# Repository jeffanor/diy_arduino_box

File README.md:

# diy_arduino_box
DIY Arduino E-Stim Unit

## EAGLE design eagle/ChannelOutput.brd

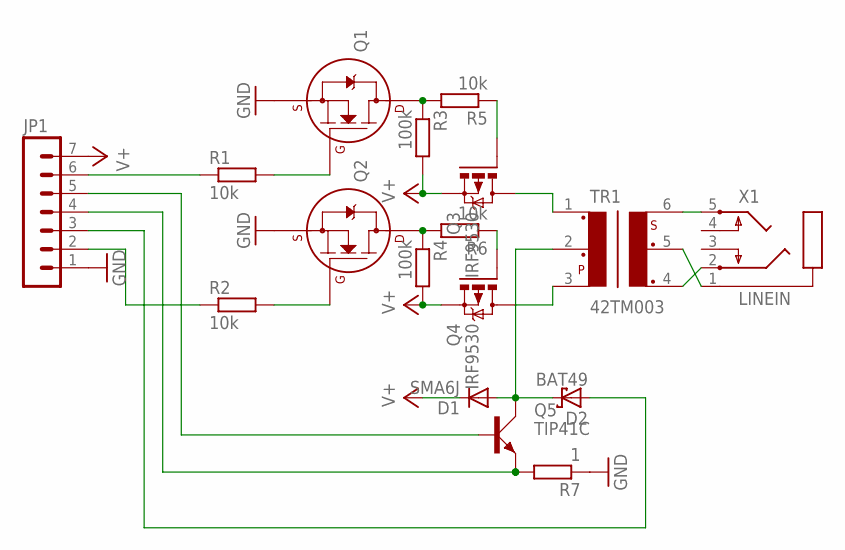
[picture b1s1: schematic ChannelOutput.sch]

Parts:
D1: SMA6J; DO41-10
D2: BAT49; DO41-10
JP1: MA07-1
Q1, Q2: 2N7000_TO92; TO-92
Q3, Q4: IRF9530; TO220BV
Q5: TIP41C; TO220AV
R1, R2, R5, R6: 10k; 0207/2V
R3, R4: 100k; 0204/5
R7: 1; 0207/2V
TR1: 42TM003; 42TM
X1: LINEIN; PG203J

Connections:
GND: JP1.1, Q1.1 (S), Q2.1 (S), R7.1
unnamed: Q1.2 (G), R1.2
unnamed: Q4.G, R6.1
unnamed: JP1.2, R2.1
unnamed: JP1.6, R1.1
unnamed: Q4.D, TR1.3
unnamed: Q3.D, TR1.1
unnamed: D2.A, JP1.3
unnamed: JP1.4, Q5.E, R7.2
unnamed: D1.A, D2.C, Q5.C, TR1.2
unnamed: TR1.6, X1.5
unnamed: TR1.5, X1.1
unnamed: TR1.4, X1.2
unnamed: Q2.3 (D), R4.1, R6.2
unnamed: Q3.G, R5.1
unnamed: Q1.3 (D), R3.1, R5.2
unnamed: Q2.2 (G), R2.2
unnamed: JP1.5, Q5.B
V+: D1.C, JP1.7, Q3.S, Q4.S, R3.2, R4.2

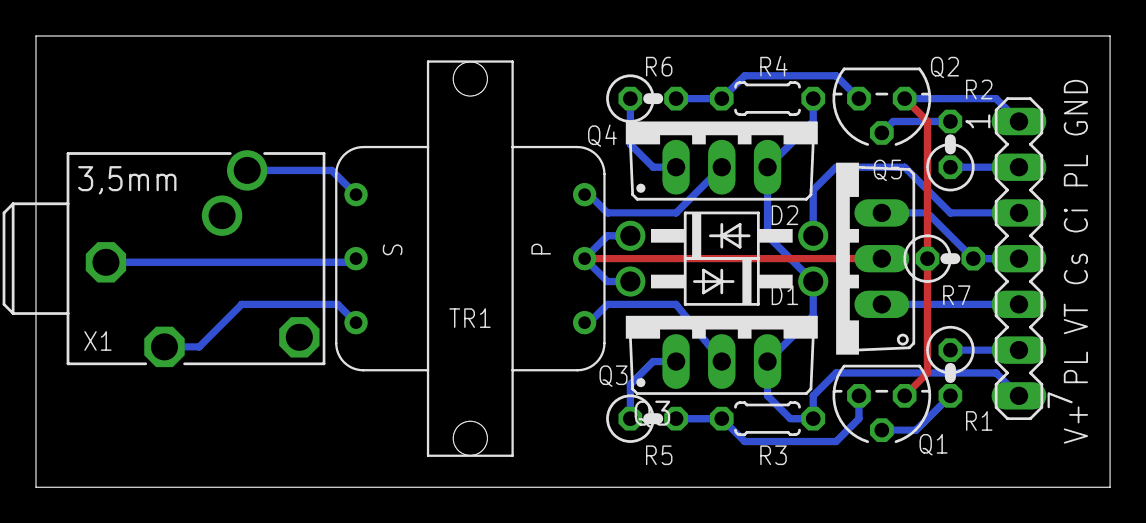
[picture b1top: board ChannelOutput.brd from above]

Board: 2 copper layers, 59.7 x 25.1 mm, 17 parts (0 on the bottom side), 19 nets.

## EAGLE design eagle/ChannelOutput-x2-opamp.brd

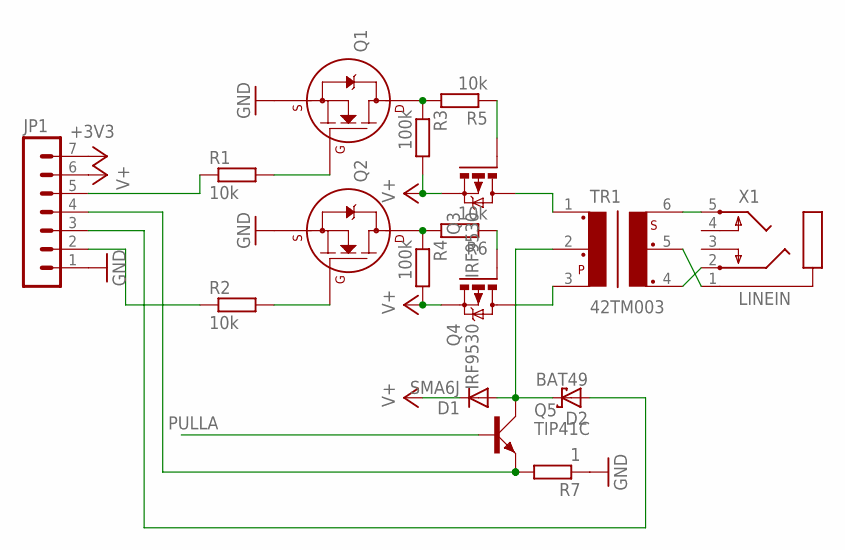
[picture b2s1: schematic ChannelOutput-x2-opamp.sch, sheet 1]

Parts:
D1: SMA6J; DO41-10
D2: BAT49; DO41-10
JP1: MA07-1
Q1, Q2: 2N7000_TO92; TO-92
Q3, Q4: IRF9530; TO220BV
Q5: TIP41C; TO220AV
R1, R2, R5, R6: 10k; 0207/2V
R3, R4: 100k; 0204/5
R7: 1; 0207/2V
TR1: 42TM003; 42TM
X1: LINEIN; PG203J

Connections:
+3V3: JP1.7; also elsewhere on the board
GND: JP1.1, Q1.1 (S), Q2.1 (S), R7.1; also elsewhere on the board
unnamed: Q1.2 (G), R1.2
unnamed: Q4.G, R6.1
unnamed: JP1.2, R2.1
unnamed: JP1.5, R1.1
unnamed: Q4.D, TR1.3
unnamed: Q3.D, TR1.1
unnamed: D2.A, JP1.3
unnamed: JP1.4, Q5.E, R7.2
unnamed: D1.A, D2.C, Q5.C, TR1.2
unnamed: TR1.6, X1.5
unnamed: TR1.5, X1.1
unnamed: TR1.4, X1.2
unnamed: Q2.3 (D), R4.1, R6.2
unnamed: Q3.G, R5.1
unnamed: Q1.3 (D), R3.1, R5.2
unnamed: Q2.2 (G), R2.2
PULLA: Q5.B; also elsewhere on the board
V+: D1.C, JP1.6, Q3.S, Q4.S, R3.2, R4.2; also elsewhere on the board

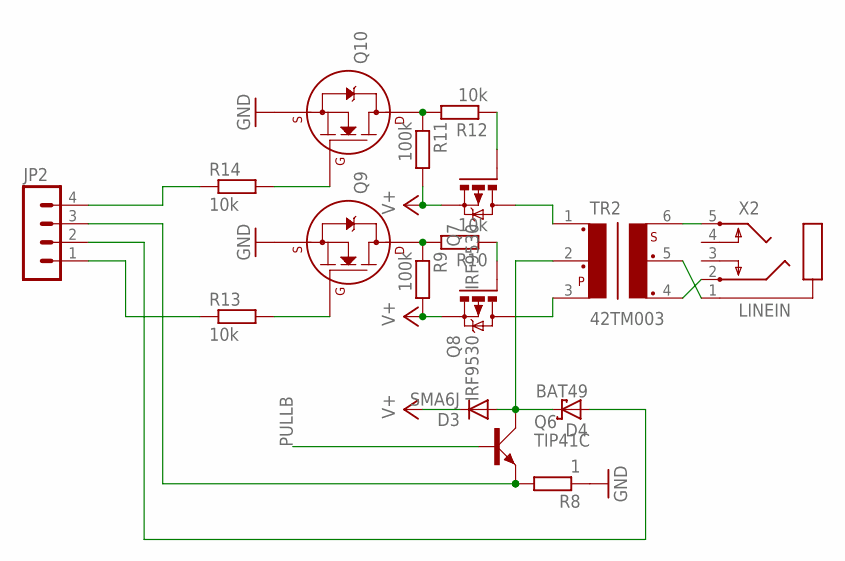
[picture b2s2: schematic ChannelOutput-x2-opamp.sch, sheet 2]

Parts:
D3: SMA6J; DO41-10
D4: BAT49; DO41-10
JP2: MA04-1
Q6: TIP41C; TO220AV
Q7, Q8: IRF9530; TO220BV
Q9, Q10: 2N7000_TO92; TO-92
R8: 1; 0207/2V
R9, R11: 100k; 0204/5
R10, R12, R13, R14: 10k; 0207/2V
TR2: 42TM003; 42TM
X2: LINEIN; PG203J

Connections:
GND: Q9.1 (S), Q10.1 (S), R8.1; also elsewhere on the board
unnamed: D3.A, D4.C, Q6.C, TR2.2
unnamed: TR2.6, X2.5
unnamed: TR2.5, X2.1
unnamed: TR2.4, X2.2
unnamed: JP2.3, Q6.E, R8.2
unnamed: Q9.3 (D), R9.1, R10.2
unnamed: Q7.G, R12.1
unnamed: Q10.3 (D), R11.1, R12.2
unnamed: Q9.2 (G), R13.2
unnamed: JP2.4, R14.1
unnamed: Q8.G, R10.1
unnamed: Q10.2 (G), R14.2
unnamed: JP2.1, R13.1
unnamed: Q8.D, TR2.3
unnamed: Q7.D, TR2.1
unnamed: D4.A, JP2.2
PULLB: Q6.B; also elsewhere on the board
V+: D3.C, Q7.S, Q8.S, R9.2, R11.2; also elsewhere on the board

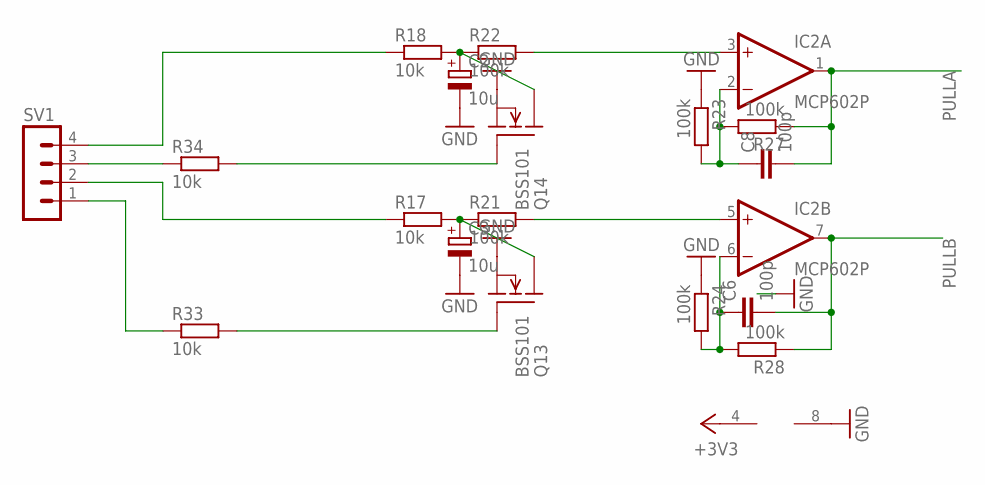
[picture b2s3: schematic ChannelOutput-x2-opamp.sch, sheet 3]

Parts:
C2, C3: 10u; TT2D5
C6, C8: 100p; C025-024X044
IC2: MCP602P; DIL08
Q13, Q14: BSS101; TO92
R17, R18, R33, R34: 10k; 0207/2V
R21, R22, R23, R24, R27, R28: 100k; 0207/2V
SV1: MA04-1

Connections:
+3V3: IC2.4 (V-); also elsewhere on the board
GND: C2.-, C3.-, IC2.8 (V+), Q13.1 (S), Q14.1 (S), R23.1, R24.1; also elsewhere on the board
unnamed: R34.1, SV1.3
unnamed: IC2.3 (+IN), R22.2
unnamed: R18.1, SV1.4
unnamed: C6.1, IC2.6 (-IN), R24.2, R28.2
unnamed: R17.1, SV1.2
unnamed: C8.1, IC2.2 (-IN), R23.2, R27.2
unnamed: Q14.2 (G), R34.2
unnamed: Q13.2 (G), R33.2
unnamed: R33.1, SV1.1
unnamed: C2.+, Q14.3 (D), R18.2, R22.1
unnamed: C3.+, Q13.3 (D), R17.2, R21.1
unnamed: IC2.5 (+IN), R21.2
PULLA: C8.2, IC2.1 (OUT), R27.1; also elsewhere on the board
PULLB: C6.2, IC2.7 (OUT), R28.1; also elsewhere on the board

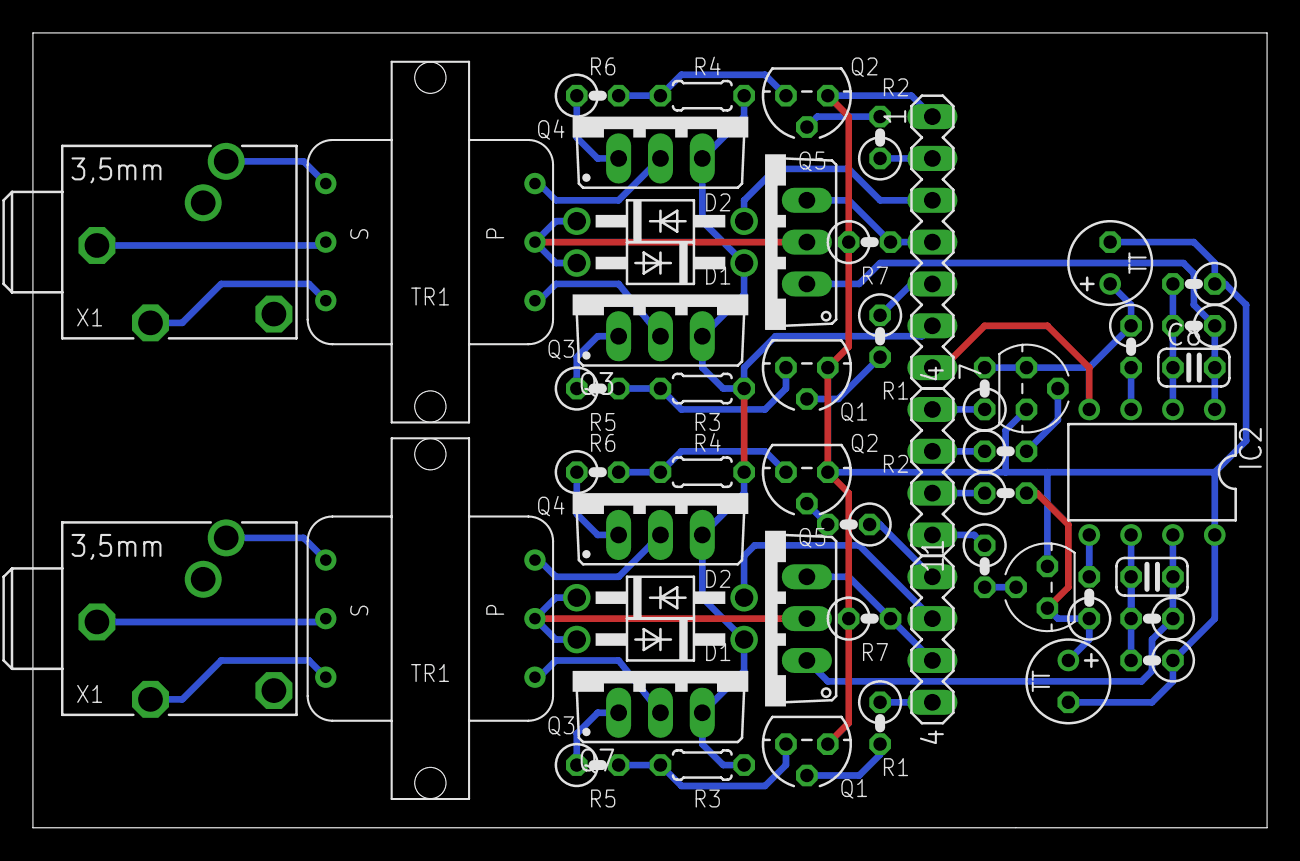
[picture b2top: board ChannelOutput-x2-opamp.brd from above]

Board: 2 copper layers, 74.9 x 48.3 mm, 52 parts (0 on the bottom side), 49 nets.

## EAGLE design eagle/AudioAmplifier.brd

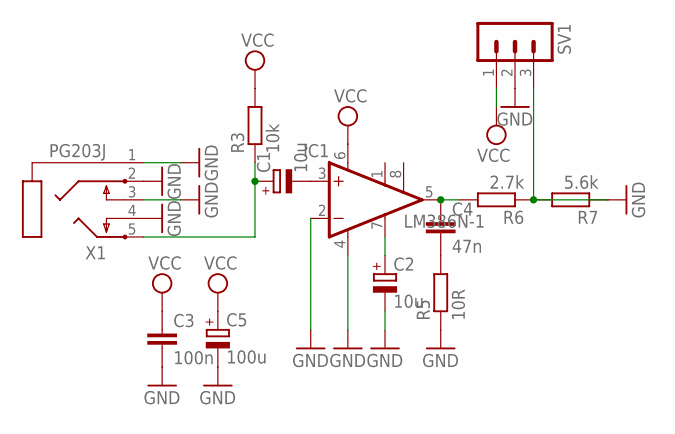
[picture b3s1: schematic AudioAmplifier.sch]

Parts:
C1, C2: 10u; TT2D5
C3: 100n; C025-024X044
C4: 47n; C025-024X044
C5: 100u; TT2D5
IC1: LM386N-1; DIL08
R3: 10k; 0204/7
R5: 10R; 0207/2V
R6: 2.7k; 0207/2V
R7: 5.6k; 0207/2V
SV1: MA03-1
X1: PG203J

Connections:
GND: C2.-, C3.2, C5.-, IC1.2 (-IN), IC1.4 (GND), R5.1, R7.2, SV1.2, X1.1, X1.2, X1.3, X1.4
unnamed: R6.1, R7.1, SV1.3
unnamed: C1.-, IC1.3 (+IN)
unnamed: C2.+, IC1.7 (BYPASS)
unnamed: C4.1, IC1.5 (OUT), R6.2
unnamed: C4.2, R5.2
unnamed: C1.+, R3.1, X1.5
VCC: C3.1, C5.+, IC1.6 (VS), R3.2, SV1.1

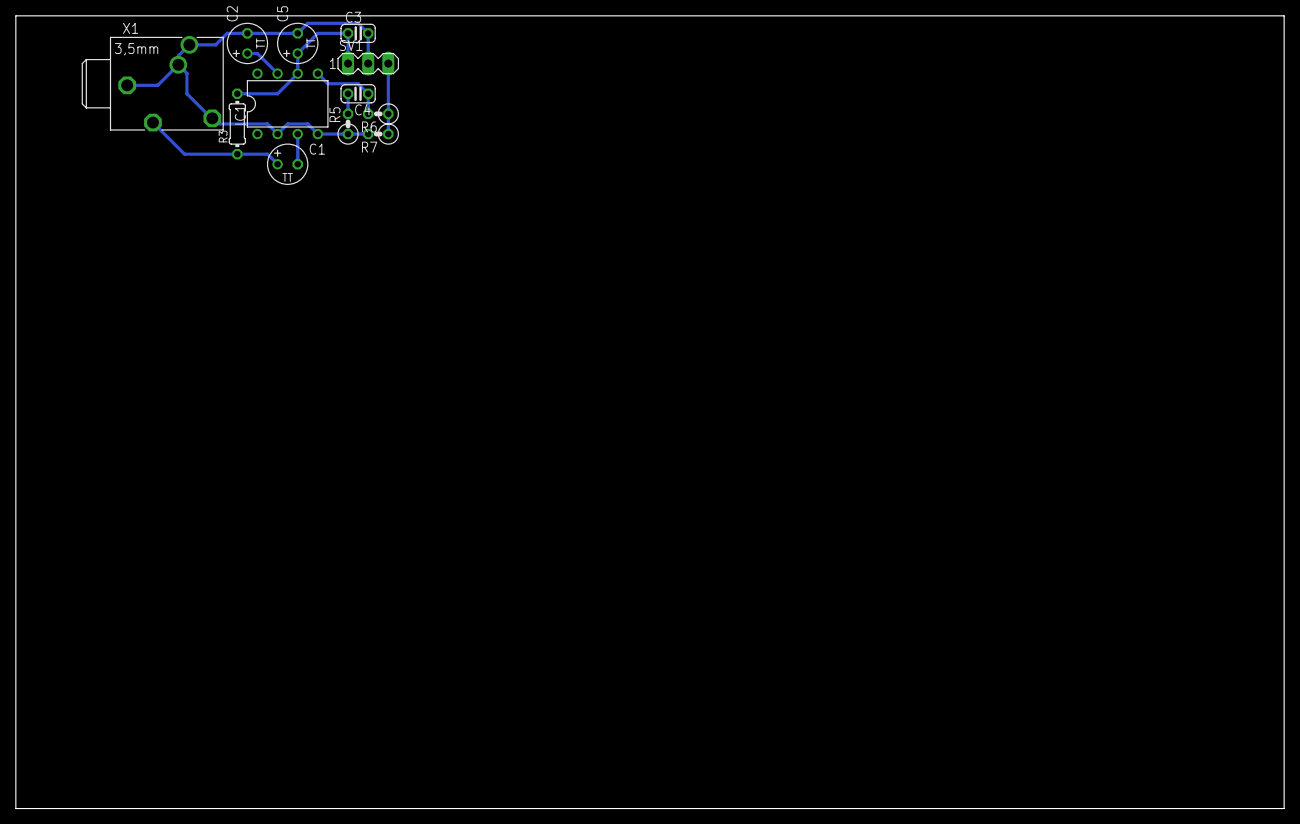
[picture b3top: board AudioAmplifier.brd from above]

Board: 2 copper layers, 160.0 x 100.0 mm, 12 parts (0 on the bottom side), 8 nets.

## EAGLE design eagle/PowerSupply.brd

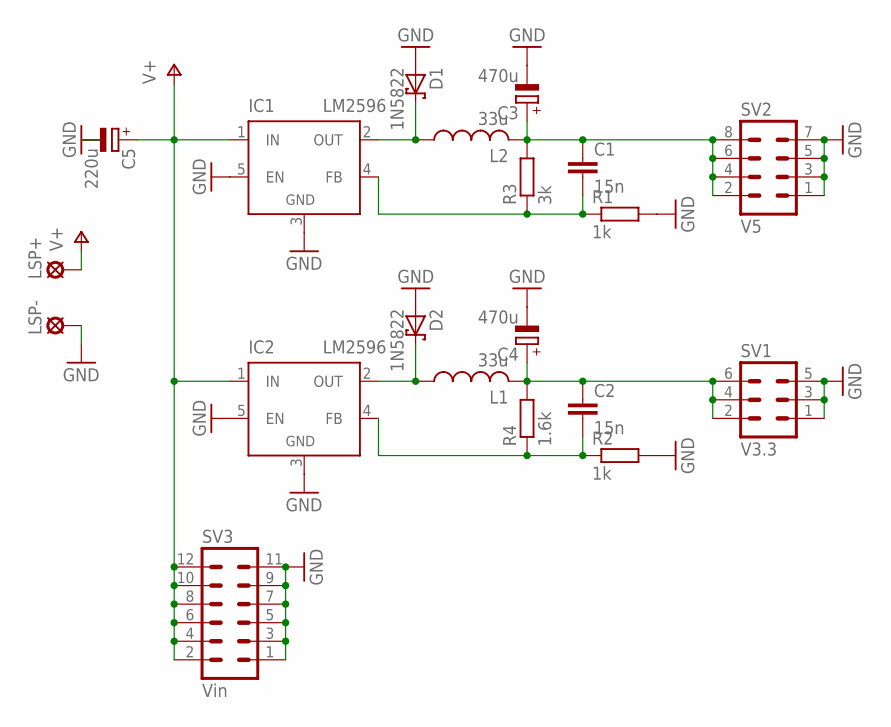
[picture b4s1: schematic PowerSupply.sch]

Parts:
C1, C2: 15n; C075-032X103
C3, C4: 470u; E2,5-6
C5: 220u; E2,5-6
D1, D2: 1N5822; DO41-7.6
IC1, IC2: LM2596; TO220-51
L1, L2: 33u; TFI0510
LSP+: SE14
LSP-: SE14
R1, R2: 1k; 0309V
R3: 3k; 0204/5
R4: 1.6k; 0204/5
SV1: V3.3; MA03-2
SV2: V5; MA04-2
SV3: Vin; MA06-2

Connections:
GND: C3.-, C4.-, C5.-, D1.A, D2.A, IC1.3 (GND), IC1.5 (EN), IC2.3 (GND), IC2.5 (EN), LSP-.MP, R1.2, R2.2, SV1.1, SV1.3, SV1.5, SV2.1, SV2.3, SV2.5, SV2.7, SV3.1, SV3.3, SV3.5, SV3.7, SV3.9, SV3.11
unnamed: C1.1, C3.+, L2.2, R3.2, SV2.2, SV2.4, SV2.6, SV2.8
unnamed: D2.C, IC2.2 (OUT), L1.1
unnamed: D1.C, IC1.2 (OUT), L2.1
unnamed: C2.1, C4.+, L1.2, R4.2, SV1.2, SV1.4, SV1.6
unnamed: C2.2, IC2.4 (FB), R2.1, R4.1
unnamed: C1.2, IC1.4 (FB), R1.1, R3.1
V+: C5.+, IC1.1 (IN), IC2.1 (IN), LSP+.MP, SV3.2, SV3.4, SV3.6, SV3.8, SV3.10, SV3.12

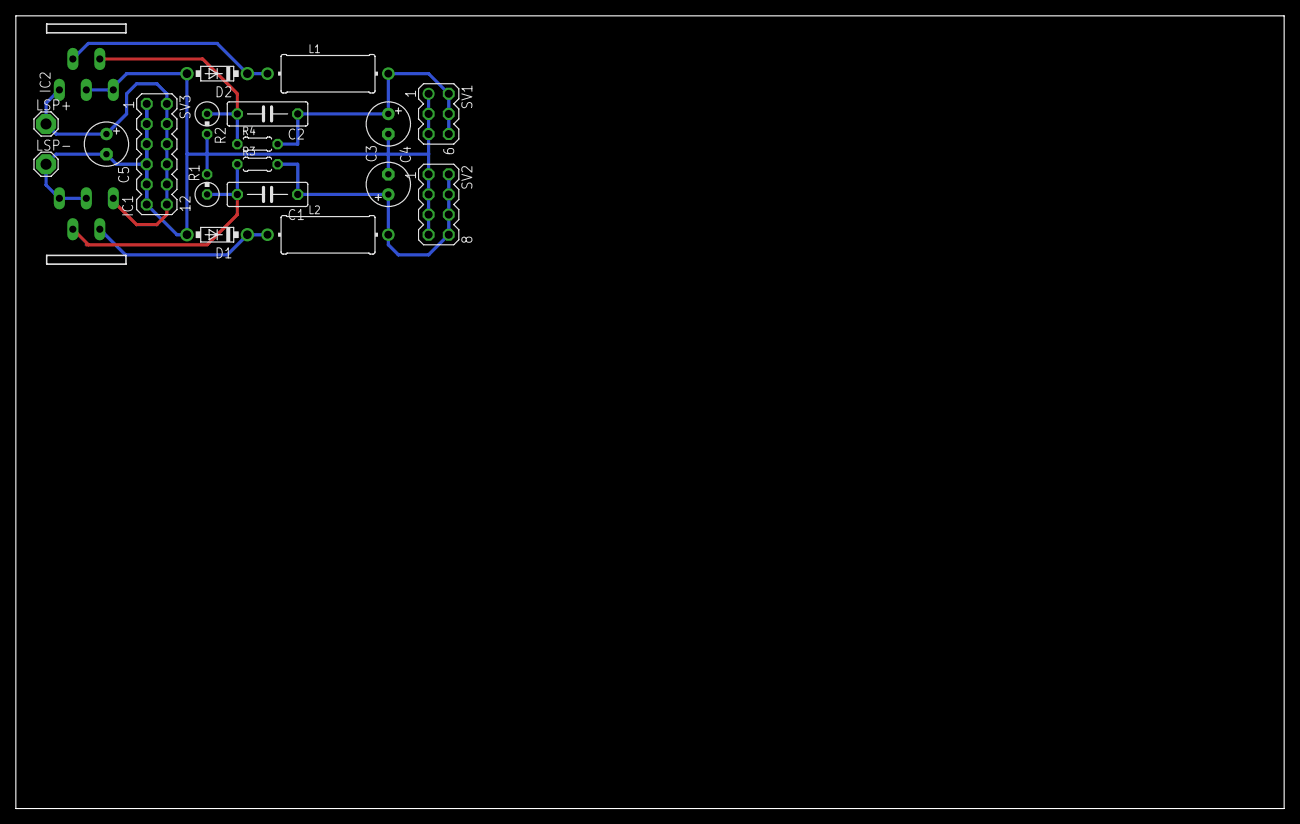
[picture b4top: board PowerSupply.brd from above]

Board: 2 copper layers, 160.0 x 100.0 mm, 20 parts (0 on the bottom side), 8 nets.

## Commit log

2016-01-02 Blog photos. Power supply eagle files. Due, LM2596, LM386, SAM3X8E data sheets.
2016-01-03 Audio Amplifier
2016-03-06 SPI and ST7735
2016-03-06 font and palette
2016-03-06 removed broken include
2016-03-06 Knob class
2016-03-06 ST7735 data sheet
2016-03-14 Output stage variants
